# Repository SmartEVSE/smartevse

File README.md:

SmartEVSE v1
=========

This repository is now for the older v1 of the module only.
All developement for the current version v2 of the module is taking place here:
[SmartEVSE-2](https://github.com/SmartEVSE/SmartEVSE-2)

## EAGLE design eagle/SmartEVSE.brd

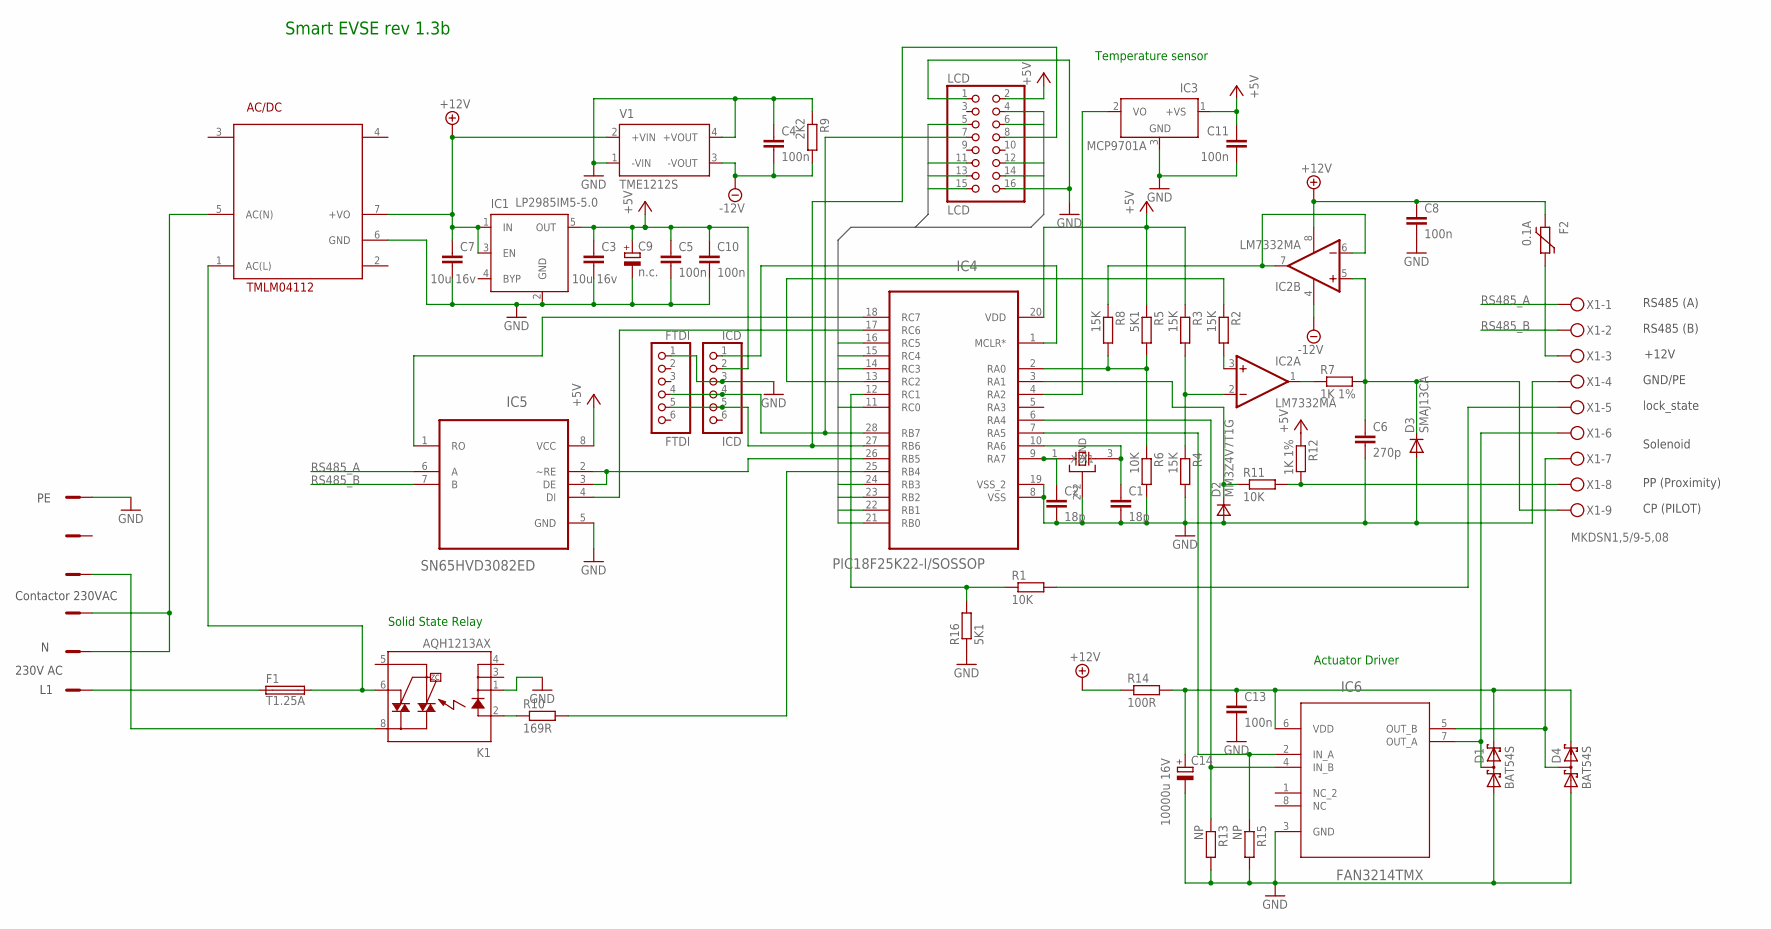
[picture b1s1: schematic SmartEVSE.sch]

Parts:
AC/DC: TMLM04112; AC/DC
C1, C2: 18p; C0805
C3, C7: 10u 16v; C1206
C4, C5, C8, C10, C11, C13: 100n; C0805
C6: 270p; C0805
C9: n.c.; SMC_C
C14: 10000u 16V; EB22,5D
D1, D4: BAT54S; SOT23
D2: MM3Z4V7T1G; SOD323
D3: SMAJ13CA; DO214AC
F1: T1.25A; TR5
F2: 0.1A; 1206L
FTDI: FTDI; 1X06
IC1: LP2985IM5-5.0; SOT23-5
IC2: LM7332MA; SO08
IC3: MCP9701A; SOT23
IC4: PIC18F25K22-I/SOSSOP; SOP65P780X200-28N
IC5: SN65HVD3082ED; SOIC127P600X175-8N
IC6: FAN3214TMX; SOIC127P600X175-8N
ICD: ICD; 1X06
K1: AQH1213AX; DIL07SMD
LCD: LCD; 2X08
Q1: CTS_32X25_SMD; CTS_32X25
R1, R6, R11: 10K; R0805
R2, R3, R4, R8: 15K; R0805
R5, R16: 5K1; R0805
R7, R12: 1K 1%; R0805
R9: 2K2; R0805
R10: 169R; R0805
R13, R15: NP; R0805
R14: 100R; R0805
V1: TME1212S; TME
X1: MKDSN1,5/9-5,08
X2: AST027-06; P_AST027-06

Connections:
+12V: AC/DC.7 (+VO), C7.1, C8.1, F2.P$1 (1), IC1.1 (IN), IC1.3 (EN), IC2.8 (V+), R14.1, V1.2 (+VIN)
-12V: C4.2, IC2.4 (V-), R9.2, V1.3 (-VOUT)
GND: AC/DC.6 (GND), C1.2, C2.2, C3.2, C4.1, C5.2, C6.2, C7.2, C8.2, C9.-, C10.2, C11.2, C13.2, C14.-, D1.1 (A1), D2.2 (A), D3.A, D4.1 (A1), FTDI.1, IC1.2 (GND), IC3.3 (GND), IC4.8 (VSS), IC4.19 (VSS_2), IC5.5 (GND), IC6.3 (GND), ICD.3, K1.1 (K), LCD.1, LCD.16, Q1.2 (GND), Q1.4 (GND), R4.2, R6.2, R9.1, R13.2, R15.2, R16.1, V1.1 (-VIN), V1.4 (+VOUT), X1.4, X2.P$1
LCD0: IC4.21 (RB0), LCD.11
LCD1: IC4.22 (RB1), LCD.12
LCD2: IC4.23 (RB2), LCD.13
LCD3: IC4.24 (RB3), LCD.14
LCD4: IC4.11 (RC0), LCD.15
LCD6: IC4.14 (RC3), LCD.4
LCD7: IC4.15 (RC4), LCD.5
LCD8: IC4.16 (RC5), LCD.6
unnamed: IC4.12 (RC1), R1.1, R16.2
unnamed: IC4.6 (RA4), IC6.4 (IN_B), R13.1
unnamed: IC4.17 (RC6), IC5.4 (DI)
unnamed: IC4.18 (RC7), IC5.1 (RO)
unnamed: C2.1, IC4.9 (RA7), Q1.1 (X1)
unnamed: C1.1, IC4.10 (RA6), Q1.3 (X2)
unnamed: IC2.2 (-IN), R3.2, R4.1
unnamed: C6.1, D3.C, IC2.5 (+IN), R7.2, X1.9
unnamed: IC4.13 (RC2), R2.1
unnamed: IC2.3 (+IN), R2.2
unnamed: IC4.2 (RA0), R5.2, R6.1, R8.2
unnamed: IC2.1 (OUT), R7.1
unnamed: IC2.6 (-IN), IC2.7 (OUT), R8.1
unnamed: D2.1 (C), IC4.3 (RA1), R11.1
unnamed: C13.1, C14.+, D1.2 (C2), D4.2 (C2), IC6.6 (VDD), R14.2
unnamed: IC4.7 (RA5), IC6.2 (IN_A), R15.1
unnamed: K1.2 (A), R10.1
unnamed: IC4.25 (RB4), R10.2
unnamed: AC/DC.1 (AC(L)), F1.2, K1.6 (DS3)
unnamed: R11.2, R12.2, X1.8
unnamed: K1.8 (DS1), X2.P$3
unnamed: F1.1, X2.P$6
unnamed: IC4.26 (RB5), IC5.2 (~RE), IC5.3 (DE)
unnamed: AC/DC.5 (AC(N)), X2.P$4, X2.P$5
unnamed: D1.3 (C1A2), IC6.7 (OUT_A), X1.6
unnamed: IC4.1 (MCLR*), ICD.1
unnamed: D4.3 (C1A2), IC6.5 (OUT_B), X1.7
unnamed: IC3.2 (VO), IC4.4 (RA2)
unnamed: F2.P$2 (2), X1.3
unnamed: R1.2, X1.5
unnamed: FTDI.4, IC4.28 (RB7), ICD.4, LCD.7
unnamed: FTDI.5, IC4.27 (RB6), ICD.5, LCD.8
RS485_A: IC5.6 (A), X1.1
RS485_B: IC5.7 (B), X1.2
VCC: C3.1, C5.1, C9.+, C10.1, C11.1, IC1.5 (OUT), IC3.1 (+VS), IC4.20 (VDD), IC5.8 (VCC), ICD.2, LCD.2, R3.1, R5.1, R12.1

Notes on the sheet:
230V AC
Solenoid
lock_state
+12V
CP (PILOT)
PP (Proximity)
GND/PE
RS485 (A)
RS485 (B)
Contactor 230VAC
Smart EVSE rev 1.3b
Temperature sensor
Actuator Driver
Solid State Relay

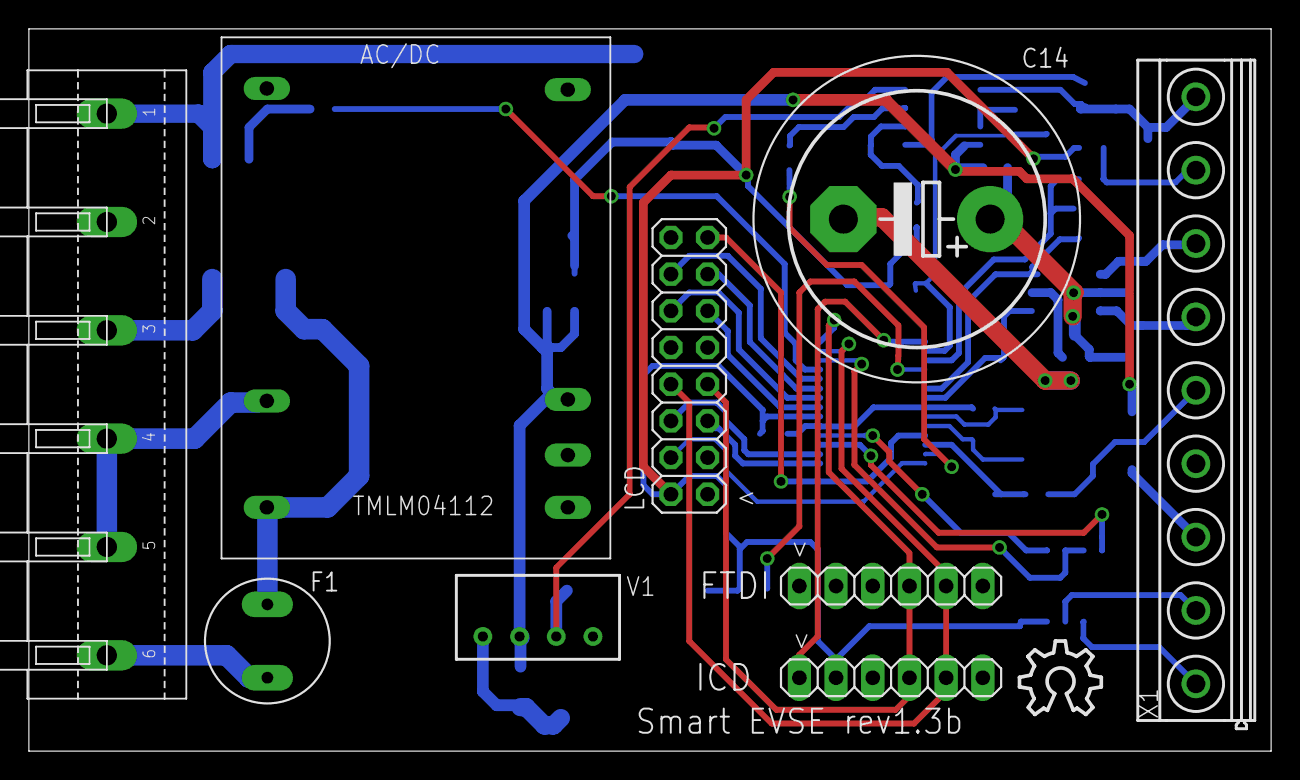
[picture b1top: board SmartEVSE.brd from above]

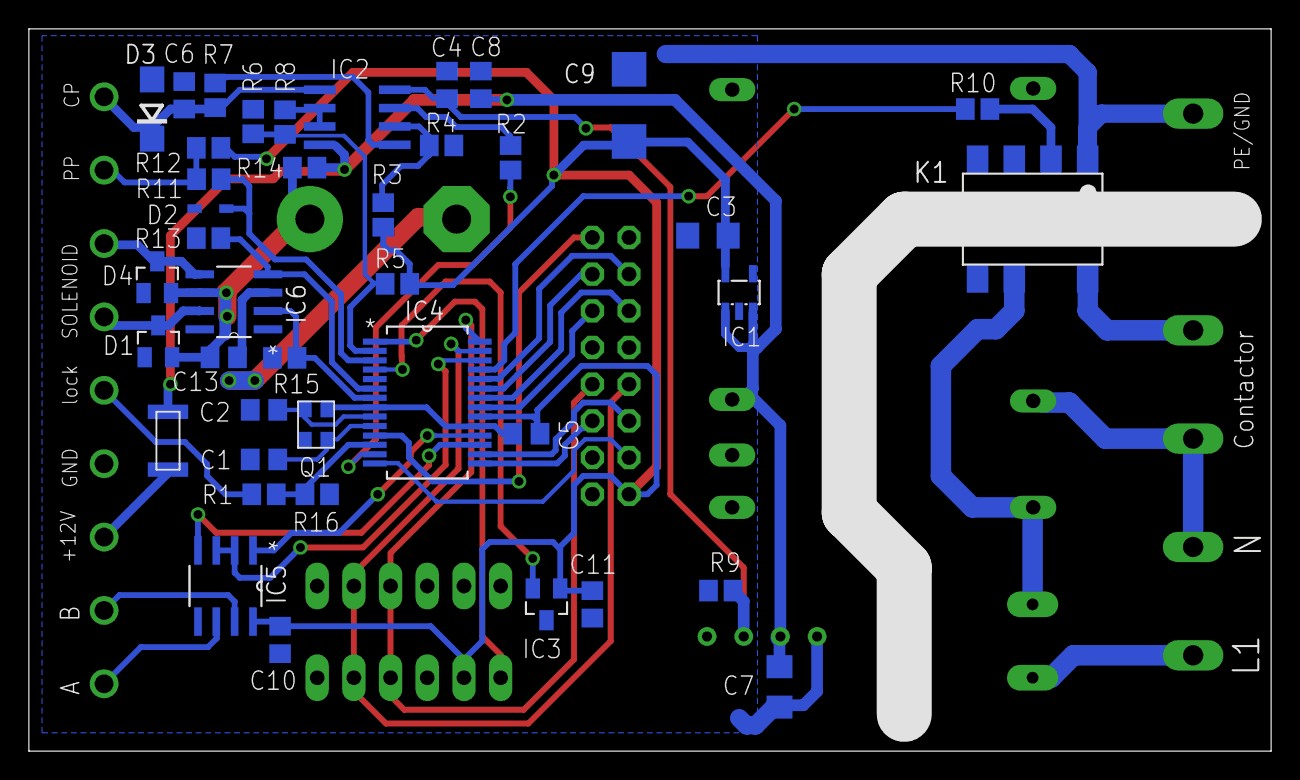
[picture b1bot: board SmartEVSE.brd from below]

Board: 2 copper layers, 86.0 x 50.0 mm, 51 parts (41 on the bottom side), 46 nets.

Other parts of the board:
U$1: OSHW_10X200_NOTEXT

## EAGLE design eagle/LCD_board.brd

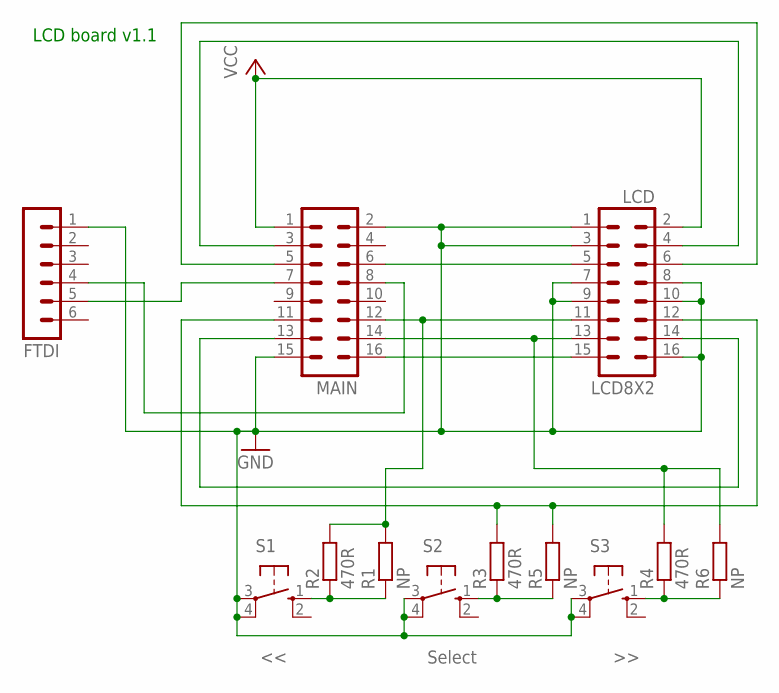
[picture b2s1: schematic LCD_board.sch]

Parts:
FTDI: MA06-1
LCD8X2: LCD; MA08-2
MAIN: MA08-2
R1, R5, R6: NP; 0204/7
R2, R3, R4: 470R; R0805
S1: <<; B3F-10XX
S2: Select; B3F-10XX
S3: >>; B3F-10XX

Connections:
GND: FTDI.1, LCD8X2.1, LCD8X2.3, LCD8X2.7, LCD8X2.8, LCD8X2.9, LCD8X2.10, LCD8X2.16, MAIN.2, MAIN.15, S1.3, S1.4 (P1), S2.3, S2.4 (P1), S3.3, S3.4 (P1)
unnamed: FTDI.5, MAIN.7
unnamed: LCD8X2.15, MAIN.16
unnamed: LCD8X2.13, MAIN.14, R4.2, R6.2
unnamed: LCD8X2.11, MAIN.12, R1.2, R2.2
unnamed: LCD8X2.14, MAIN.13
unnamed: LCD8X2.12, MAIN.11, R3.2, R5.2
unnamed: LCD8X2.5, MAIN.6
unnamed: LCD8X2.6, MAIN.5
unnamed: LCD8X2.4, MAIN.3
unnamed: FTDI.4, MAIN.8
unnamed: R1.1, R2.1, S1.1 (S)
unnamed: R3.1, R5.1, S2.1 (S)
unnamed: R4.1, R6.1, S3.1 (S)
VCC: LCD8X2.2, MAIN.1

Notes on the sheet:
LCD board v1.1

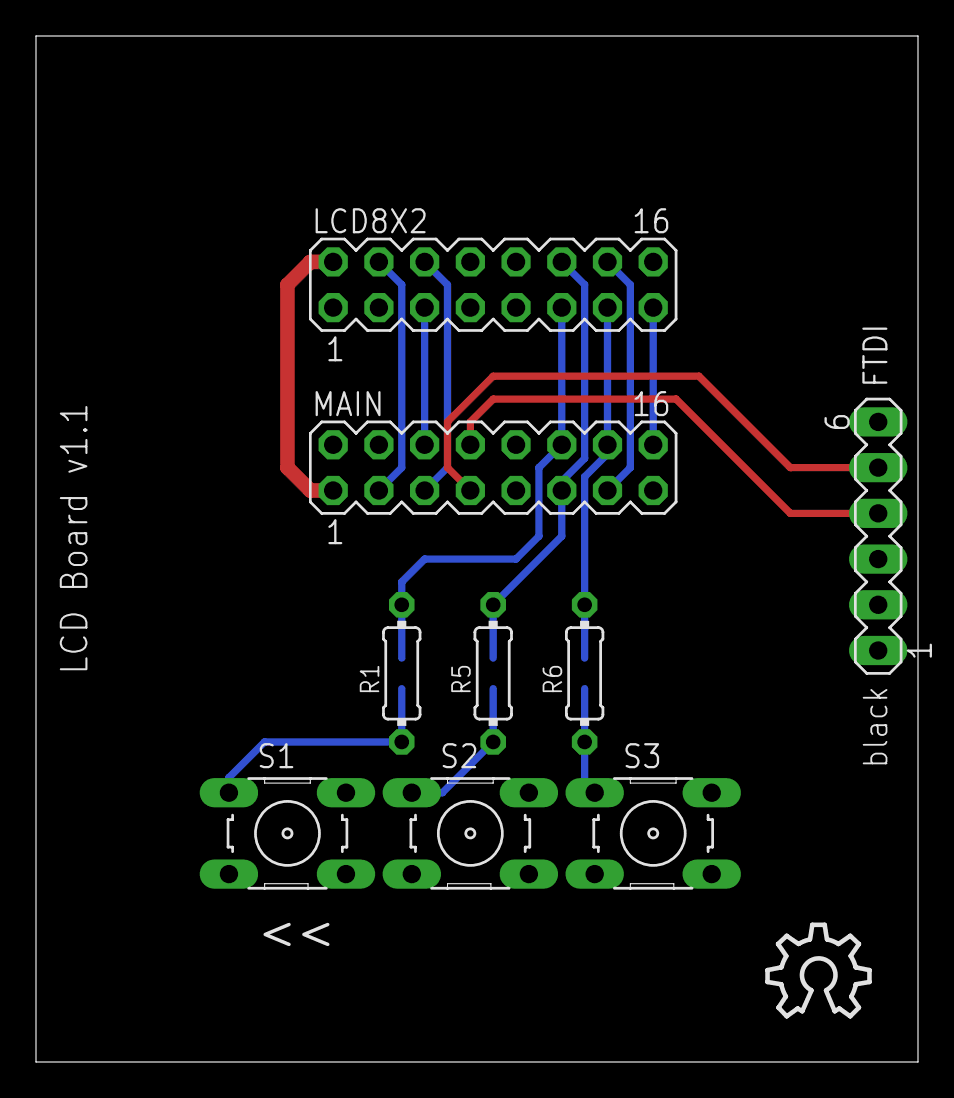
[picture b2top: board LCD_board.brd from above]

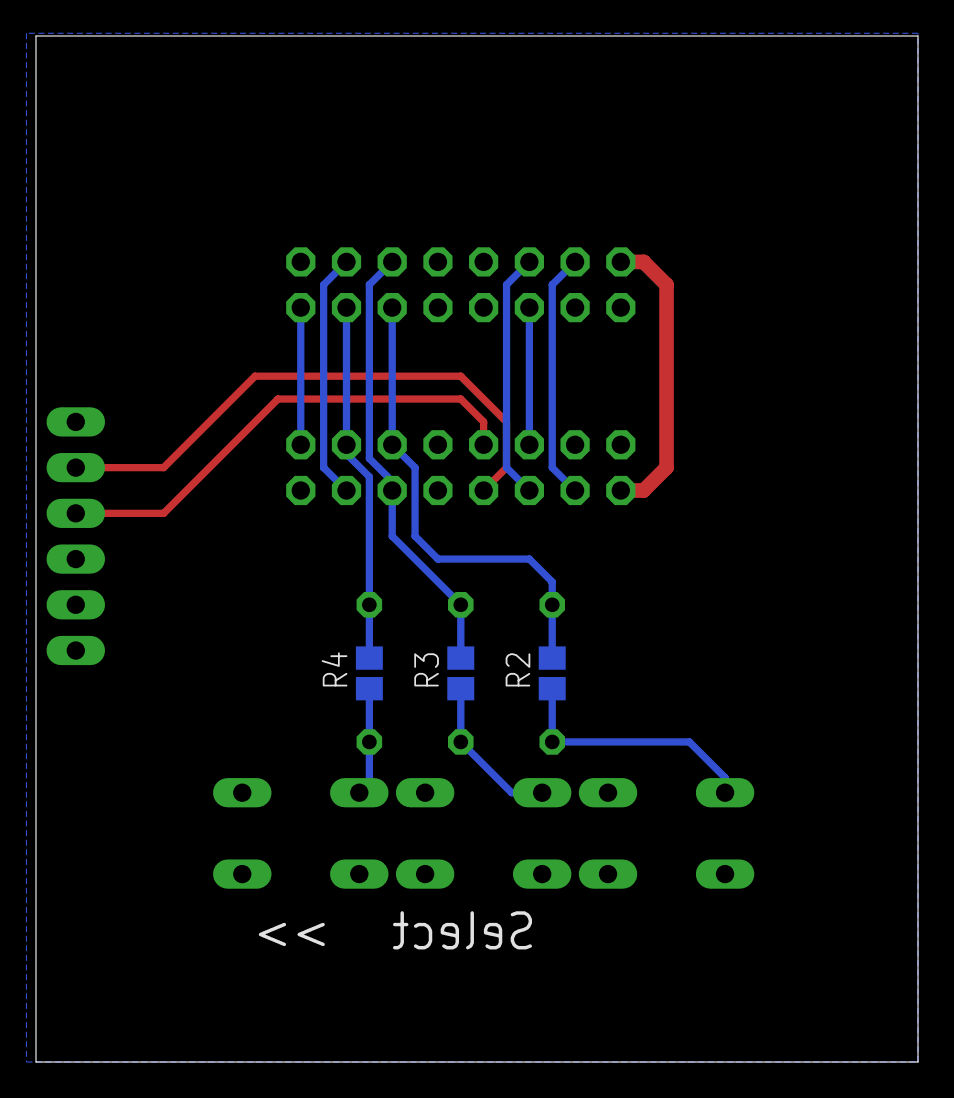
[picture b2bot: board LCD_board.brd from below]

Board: 2 copper layers, 49.0 x 57.0 mm, 13 parts (3 on the bottom side), 15 nets.

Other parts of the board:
U$1: OSHW_10X200_NOTEXT

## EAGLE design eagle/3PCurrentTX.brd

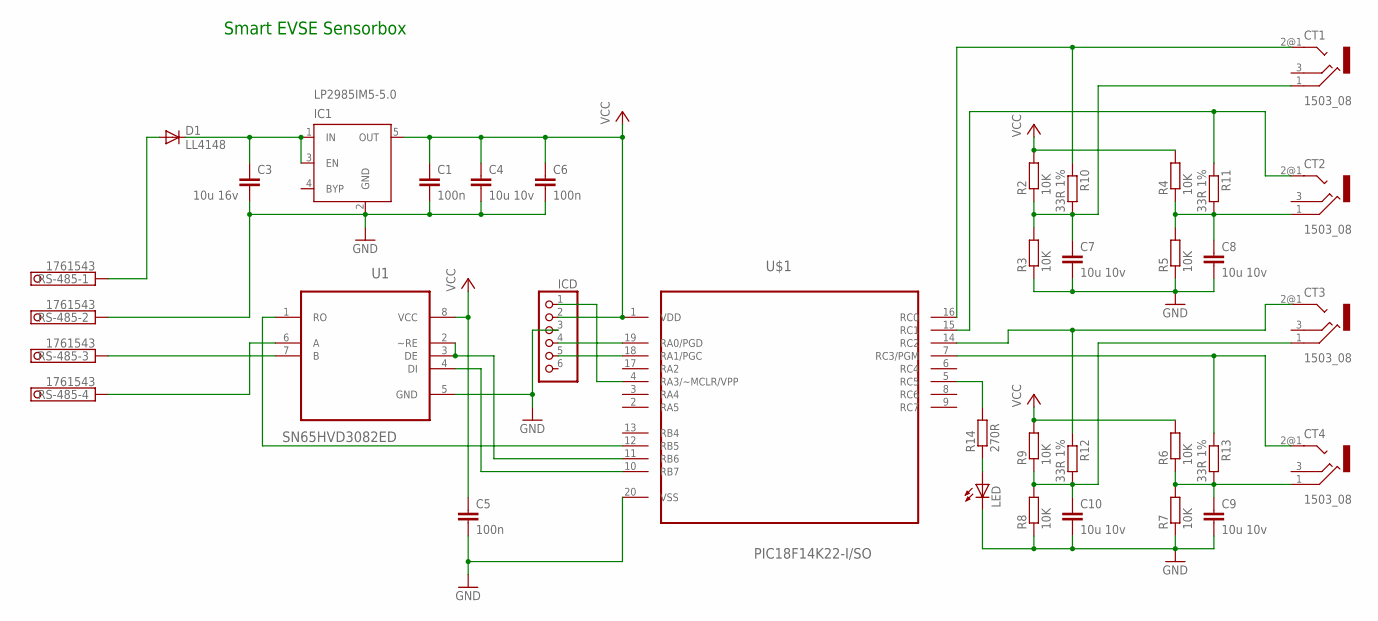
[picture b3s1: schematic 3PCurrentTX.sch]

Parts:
C1, C5, C6: 100n; C0805K
C3: 10u 16v; C1206K
C4, C7, C8, C9, C10: 10u 10v; C0805K
CT1, CT2, CT3, CT4: 1503_08
D1: LL4148; SOD123
IC1: LP2985IM5-5.0; SOT23-5
ICD: PINHD-1X6; 1X06
LED: LEDSML0805; SML0805
R2, R3, R4, R5, R6, R7, R8, R9: 10K; R0805
R10, R11, R12, R13: 33R 1%; R0805
R14: 270R; R0805
RS-485: 1761543; 1751264
U1: SN65HVD3082ED; SOIC127P600X175-8N
U$1: PIC18F14K22-I/SO; SOIC127P1030X265-20N; MPN PIC18F14k22-I/SO

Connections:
GND: C1.2, C3.2, C4.2, C5.2, C6.2, C7.2, C8.2, C9.2, C10.2, IC1.2 (GND), ICD.3, LED.C, R3.1, R5.1, R7.1, R8.1, RS-485.2, U1.5 (GND), U$1.20 (VSS)
unnamed: D1.A, RS-485.1
unnamed: R14.2, U$1.5 (RC5)
unnamed: U1.1 (RO), U$1.12 (RB5)
unnamed: U1.4 (DI), U$1.10 (RB7)
unnamed: U1.2 (~RE), U1.3 (DE), U$1.11 (RB6)
unnamed: CT1.2@1 (2), R10.1, U$1.16 (RC0)
unnamed: LED.A, R14.1
unnamed: CT3.2@1 (2), R12.1, U$1.14 (RC2)
unnamed: CT4.2@1 (2), R13.1, U$1.7 (RC3/PGM)
unnamed: CT2.2@1 (2), R11.1, U$1.15 (RC1)
unnamed: RS-485.3, U1.7 (B)
unnamed: RS-485.4, U1.6 (A)
unnamed: C7.1, CT1.1, R2.1, R3.2, R10.2
unnamed: C3.1, D1.C, IC1.1 (IN), IC1.3 (EN)
unnamed: ICD.5, U$1.18 (RA1/PGC)
unnamed: C8.1, CT2.1, R4.1, R5.2, R11.2
unnamed: ICD.1, U$1.4 (RA3/~MCLR/VPP)
unnamed: C10.1, CT3.1, R8.2, R9.1, R12.2
unnamed: C9.1, CT4.1, R6.1, R7.2, R13.2
unnamed: ICD.4, U$1.19 (RA0/PGD)
VCC: C1.1, C4.1, C5.1, C6.1, IC1.5 (OUT), ICD.2, R2.2, R4.2, R6.2, R9.2, U1.8 (VCC), U$1.1 (VDD)

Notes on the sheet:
Smart EVSE Sensorbox

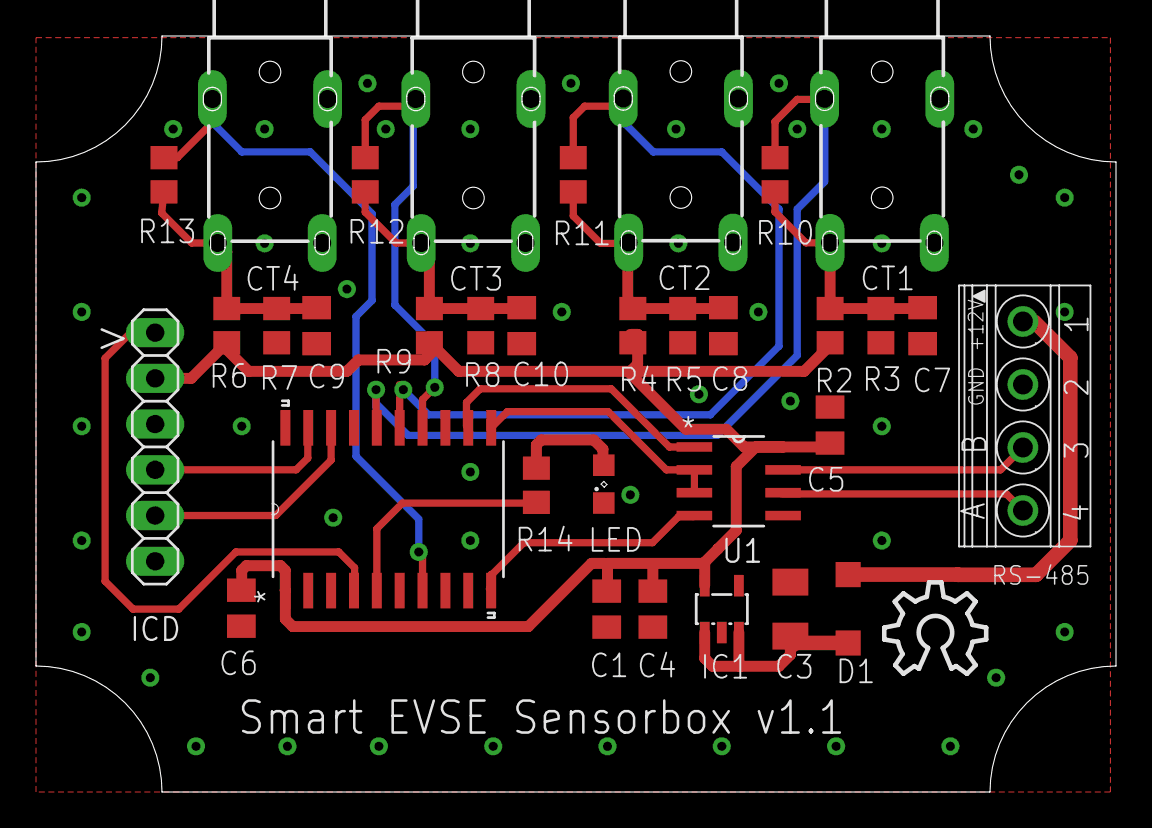
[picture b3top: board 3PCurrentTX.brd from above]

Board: 2 copper layers, 60.0 x 42.0 mm, 34 parts (0 on the bottom side), 22 nets.

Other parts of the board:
U$2: OSHW_10X200_NOTEXT

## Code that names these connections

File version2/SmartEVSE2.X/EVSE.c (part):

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        delay(3000);                                                            // wait 3 seconds for capacitor to charge

        CCP1CON = 0;                                                            // PWM off
        PORTCbits.RC2 = 0;                                                      // Control pilot static -12V
        delay(100);                                                             // wait 100 msec
        if (ReadPilot() == PILOT_DIODE) TestState = STATE_B;                    // should be -12V
        else error = 1;
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        TRISB = 0b10000101;                                                     // RB7(RX2), RB0,2 inputs. all other output
        LATBbits.LATB1 = 1;                                                     // set IO3 to high
        delay(5000);                                                            // wait 5 seconds for capacitor to charge
        if (PORTCbits.RC1 == 1) error ^= 4;                                     // error, Solenoid not activated !

        delay(10);
                                                                                // Contactor + I/O test
        if (PORTBbits.RB2 == 1)                                                 // sample input PIN IO2
        {
            LATBbits.LATB1 = 0;
            delay(10);
            if (PORTBbits.RB2 != 0) error ^= 8;                                 // error
        } else error ^= 8;                                                      // error

        TestState = STATE_CB;
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    } else if (TestState == STATE_CB && State == STATE_B) {
        TRISB = 0b10000001;                                                     // RB7(RX2), RB0 inputs. all other output
        delay(1000);
        if (PORTCbits.RC1 == 0) error ^= 4;                                     // Solenoid FAIL!!
        else if (!error) {
            TestState = 80;
            Lock = 0;
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    PMD2 = 0b00000000;

    PORTA = 0;                                                                  // Init PORTA
    ANSELA = 0b00000111;                                                        // RA0, RA1, RA2 are analog inputs (pin 2,3,4)
    TRISA = 0b00000111;                                                         // Set RA0,RA1,RA2 as inputs

    PORTB = 0;
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        
        BlinkLed();                                                             // Handle the blinking of the 12V LED

        TRISC = 0b10100011;                                                     // Set RC5 and RC0 to input. Make sure there are pull-ups on these pins.
        NOP();
        NOP();
        x = (PORTC & 0b00100001);                                               // Read Two Button Inputs on RC5(>) and RC0(select)
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
        if (RCmon == 1 && PORTBbits.RB1 == 1)                                   // RCD monitor active, and RCD DC current > 6mA ?
        {
           if (PORTBbits.RB1 == 1) {                                            // check again, to prevent voltage spikes from tripping the RCD detection (2.07)
                State = STATE_A;
                Error = RCD_TRIPPED;
                LCDTimer = 0;                                                   // display the correct error message on the LCD
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        if (State == STATE_A)                                                   
        {
            CCP1CON = 0;                                                        // PWM off
            PORTCbits.RC2 = 1;                                                  // Control pilot static +12V
            CONTACTOR_OFF;                                                      // Contactor OFF
            BalancedState[0] = 0;                                               // Mark as inactive

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                    State = STATE_ACTSTART;
                    ActivationTimer = 3;
                    CCP1CON = 0;                                                // PWM off
                    PORTCbits.RC2 = 0;                                          // Control pilot static -12V
                    INFO_PRINT("Activation Mode Triggered\r\n");
                }
                NextState = 0;                                                  // no State to switch to
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        
        if (State == STATE_ACTSTART && ActivationTimer == 0) {
            State = STATE_B;                                                    // Switch back to State B
            PORTCbits.RC2 = 1;                                                  // Control pilot static +12V
            ActivationMode = 255;                                               // Disable ActivationMode
            STATE_PRINT("STATE ACTSTART");
        }
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
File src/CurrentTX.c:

/*
;    Project:       3+ Phase Current Transmitter, for use with Smart EVSE
;    Date:          16 October 2013
;
;    Changes:
;    1.0  Initial release
;
;    (C) 2013  Michael Stegen / Stegen Electronics
;
;	 RMS current measurement calculation, from openenergymonitor.org
;
;
; Permission is hereby granted, free of charge, to any person obtaining a copy
; of this software and associated documentation files (the "Software"), to deal
; in the Software without restriction, including without limitation the rights
; to use, copy, modify, merge, publish, distribute, sublicense, and/or sell
; copies of the Software, and to permit persons to whom the Software is
; furnished to do so, subject to the following conditions:
;
; The above copyright notice and this permission notice shall be included in
; all copies or substantial portions of the Software.
;
; THE SOFTWARE IS PROVIDED "AS IS", WITHOUT WARRANTY OF ANY KIND, EXPRESS OR
; IMPLIED, INCLUDING BUT NOT LIMITED TO THE WARRANTIES OF MERCHANTABILITY,
; FITNESS FOR A PARTICULAR PURPOSE AND NONINFRINGEMENT. IN NO EVENT SHALL THE
; AUTHORS OR COPYRIGHT HOLDERS BE LIABLE FOR ANY CLAIM, DAMAGES OR OTHER
; LIABILITY, WHETHER IN AN ACTION OF CONTRACT, TORT OR OTHERWISE, ARISING FROM,
; OUT OF OR IN CONNECTION WITH THE SOFTWARE OR THE USE OR OTHER DEALINGS IN
; THE SOFTWARE.
*/


#include "p18f14k22.h"
#include <stdio.h>
#include <math.h>


// Configuration settings
#pragma	config FCMEN = OFF,	IESO = OFF, PCLKEN = ON
#pragma config PLLEN = ON, FOSC = IRC
#pragma	config BORV = 30, BOREN = OFF, PWRTEN = ON
#pragma	config WDTPS = 2048, WDTEN = OFF     // WDT timeout
#pragma config MCLRE  = OFF, HFOFST = OFF
#pragma config XINST = ON, BBSIZ = OFF, LVP = OFF, STVREN = ON
#pragma	config CP0 = OFF, CP1 = OFF, CPD = OFF, CPB = OFF
#pragma	config WRT0 = OFF, WRT1 = OFF
#pragma	config WRTD = OFF, WRTB = OFF, WRTC = OFF
#pragma	config EBTR1 = OFF, EBTR0 = OFF
#pragma	config EBTRB = OFF

// Global data
#pragma udata

#define VERSION 1
#define SAMPLES 2048				// Samples per channel
#define BAUD1K2						// Baudrate 1200 bps
#define NR_CTS	3					// Number of CT's	

char buffer[50];
double Irms[NR_CTS];
unsigned int lastSampleI,sampleI;   //sample_ holds the raw analog read value, lastSample_ holds the last sample
double lastFilteredI, filteredI;	//Filtered_ is the raw analog value minus the DC offset

unsigned int sampleI_CT[NR_CTS]={512,512,512};
double filteredI_CT[NR_CTS]={0,0,0};



void UartTX(char byte) 
{
	// output one byte 
	while(!PIR1bits.TXIF)			// set when register is empty 
		continue;
	TXREG = byte;
}

/*
void UartTXHex(unsigned char c)
{
	unsigned char h;
	
	h = (c>>4);
	if (h>9) h+=7;
	h+='0';						// conversion to ASCII
	UartTX(h);					// TX 

	h = c & 0x0f;
	if (h>9) h+=7;
	h+='0';						// conversion to ASCII
	UartTX(h);
}
*/



// calculates 16-bit CRC of given data
// used for Frame Check Sequence on data frame
// Poly used is x^16+x^12+x^5+x
unsigned int calc_crc16(char* start, char len)
{
	unsigned int crc=0xffff,c;
	int i;
	while(len--)
	{
  		c=*start;
  		for(i=0;i<8;i++)
		{
   			if((crc ^ c) & 1) crc=(crc>>1)^0x8408;
   			else crc>>=1;
   			c>>=1;
  		}
  		start++;
 	}
	crc = (unsigned int)(crc ^ 0xFFFF);
 	return(crc);
}




void UART_RX(void)
{
	char x;
	x = RCREG;						// read USART byte to clear PIR1bits.RCIF flag
									// No further processing is done at this time 
}


/*  Send buffer over RS485. Use PPP in HDLC-like Framing for transfers
;   for protocol spec see: http://tools.ietf.org/html/rfc1662
;   compatible with existing RS485 line used on SMA solar inverters.
;
; 	baudrate is 1200 bps
; 	
;	<protocol>,<version>,<nr of samples>,<sample 1>...<sample n>,<crc16>
;   protocol = 0x5001 (2 bytes)
;	version = 0x01 (1 byte) 
;	nr of channels = 1 byte
;	samples are 4 bytes (double)
;	crc16 is 2 bytes
;
;	total 4+(n*4)+2 bytes (+ HDLC overhead)
;
*/
void UART_SendBuf(char* buffer, unsigned char len)
{
	char ch;
	PORTBbits.RB6 = 1;					// set RS485 transceiver to transmit
	UartTX(0x7E);						// transmit sync flag

	while(len--)			
	{
		ch = *buffer++;					// load next byte
		if ((ch == 0x11) || (ch == 0x12) || (ch == 0x13) || (ch == 0x7E) || (ch == 0x7D))	// check for escape character
		{
			ch = ch^0x20;
			UartTX(0x7D);				// transmit escape character
		}
		UartTX(ch);						// transmit byte
	}
	
	UartTX(0x7E);						// transmit sync flag

	while (!TXSTAbits.TRMT)	continue;	// transmit register empty?
	PORTBbits.RB6 = 0;					// set RS485 transceiver to receive

}



unsigned int ReadAnalog(void)	// Start ADC conversion, and return result
{
	ADCON0bits.GO=1;						// initiate conversion on the selected channel
	while(ADCON0bits.GO);
	return ADRES;							// return result
}

double ReadCT(unsigned char Ch)
{
	unsigned int n;
	double sumI;			//sum = Sum
	unsigned char ADCch;

	ADCch=Ch+4;				// Set ADC channel
	ADCch=(ADCch<<2)+1;		// shift 2 pos to left, enable ADC
	ADCON0=ADCch;			// channel select

	sumI = 0;

	sampleI=sampleI_CT[Ch];										// Get Sample and Filter values
	filteredI=filteredI_CT[Ch];	

	for (n = 0; n < SAMPLES; n++)
  	{
    	lastSampleI = sampleI;									// Used for offset removal
    	sampleI = ReadAnalog();									// Read port RAx 
    	lastFilteredI = filteredI;								// Used for offset removal
    	filteredI = (0.996*(lastFilteredI+sampleI-lastSampleI)); 	// Digital high pass filters to remove 2.5V DC offset. 
		
		// Root-mean-square method current
	   	// 1) square current values
       	// 2) sum 
    	sumI += (filteredI * filteredI);
	}

	sampleI_CT[Ch]=sampleI;
	filteredI_CT[Ch]=filteredI;									// Store Sample and Filter values

	return (sqrt(sumI / SAMPLES));								// Return squareroot of uncalibrated value

}

void init(void)
{
	OSCCON = 0b11100000;	// setup 32Mhz internal oscillator (max 64Mhz)
	PORTA = 0; 				// Init PORTA
 	LATA = 0;
	ANSEL = 0b11110000;		// RC0, RC1, RC2, RC3 are analog inputs (pin 16,15,14,7)
	ANSELH = 0;				// All digital IO
	TRISA = 0b00100000;		// Set UART RX as input
	PORTC = 0;
	TRISC = 0b00001111;		// RC0-RC3 analog inputs
	PORTB = 0;
	TRISB = 0b00000000;		// all outputs



#if defined(BAUD19K2)
	SPBRGH = 1;				// Initialize UART
	SPBRG = 160;			// Baudrate 19k2 
#endif
#if defined(BAUD4K8)
	SPBRGH = 6;				// Initialize UART
	SPBRG = 130;			// Baudrate 4800
#endif	
#if defined(BAUD1K2)
	SPBRGH = 0x1A;			// Initialize UART
	SPBRG = 0x0A;			// Baudrate 1200
#endif	
	BAUDCON = 0b00001000;	// 16 bit Baudrate register is used
	TXSTA = 0b00100100;		// Enable TX, 8 bit, Asynchronous mode
	RCSTA = 0b10010000;		// Enable serial port TX and RX, 8 bit. 

	ADCON0 = 0;				// ADC disabled for now
	ADCON1 = 0;
	ADCON2 = 0b10000010;	// Right justify, Tacq = 0 uS, FOSC/32

	T0CON = 0b10000111;		// @ 8Mhz => 32 uS Timer0, 16 bit counter

}

void main(void)
{
	char *pBytes;
	char x,n;
	unsigned int cs;

	init();						// initialize ports, ADC, UART
	
	for (x=0;x<NR_CTS;x++)				// initialize the CT's / ADC registers
			Irms[x] = ReadCT(x);		// Read CT1..CTX, and ignore..


	while(1)
	{
		for (x=0;x<NR_CTS;x++)
			Irms[x] = ReadCT(x);		// Read CT1..CTX

		TMR0H =0;
		TMR0L =0;						// reset timer 0

		do {
			if (PIR1bits.RCIF)			// Uart Reception?
			{
				UART_RX();				// yes, read received byte
				TMR0H =0;
				TMR0L =0;				// reset timer 0
			}
			if (RCSTAbits.OERR)			// Uart Overrun Error?
			{
				RCSTAbits.CREN = 0;
				RCSTAbits.CREN = 1;		// Restart Uart
			}
			x= TMR0L;					// Read TMR0 
		} while (TMR0H < 5);			// no data on RS485 line for 40 ms 

										// Setup HDLC frame
		buffer[0]= 0xff;				// Address Field = ff
		buffer[1]= 0x03;				// Control Field = 03
		buffer[2]= 0x50;				// Protocol = 0x5001
		buffer[3]= 0x01;
		buffer[4]= VERSION;
		buffer[5]= NR_CTS;

		n=6;
		for (x=0;x<NR_CTS;x++)
		{	
			pBytes = (char*)&Irms[x];	// get raw 4 byte Double 
			buffer[n++] = (pBytes[0]);
			buffer[n++] = (pBytes[1]);
			buffer[n++] = (pBytes[2]);
			buffer[n++] = (pBytes[3]);
		}
										// Frame Check Sequence (FCS) Field
		cs = calc_crc16(buffer, n);		// calculate CRC16 from data			
		buffer[n++] = ((unsigned char)(cs));
		buffer[n++] = ((unsigned char)(cs>>8));	

		PORTCbits.RC5=1;				// LED on
		UART_SendBuf(buffer,n);			// send buffer to RS485 port
		PORTCbits.RC5=0;				// LED off

	//	printf("CT1:%5d CT2:%5d CT3:%5d\r\n",(int)(Irms[0]*100), (int)(Irms[1]*100), (int)(Irms[2]*100));
	}
 

}

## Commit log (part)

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2014-01-07 First commit of Smart EVSE
2014-01-20 Second commit of Smart EVSE
2015-07-04 doc: Add CLI docs
2015-07-04 doc: Add a picture with a TTL cable connected
2016-02-23 Version 1.04
    Changed menu so that only relevant options are shown. Added option for fixed cable installations. (no Cable Lock, override PP pin) ;
2016-03-15 version 1.06, Improved Smartmode current regulation
2016-06-10 version 1.07 Added Load balancing option for 2-4 SmartEVSE's.
2017-08-28 Smart EVSE v2 code and pcb files
2018-04-26 Changed minimal MaxMains value to 16A
    See https://github.com/SmartEVSE/smartevse/issues/7
2018-10-08 Add picture SmartEVSEv2
2018-11-03 Whitespace changes
    I saw that the file was mixing tabs and spaces for indentation.
    As I was fixing that, I also went a bit overboard with the outlining of the comments :-)
2019-02-18 Version 2.04
    In version 2.04 we added support for external stop button, a 12V LED on IO1.
    The external 12V LED requires a hardware change (hw ver 2.1)
2019-02-24 typo
2019-04-24 V2.06
    Firmware version 2.06
2019-05-13 Change some lines to windows line ending
2019-05-13 Automate LCD menu generation for easier code reading and maintenance
2019-05-14 Add experimental modbus functions
2019-05-22 Bugfix: Cant navigate back from the lowest value to the highest if the lowest value is 0
2019-05-26 Add Solar mode and animated graphic
2019-05-26 Simplify GLCDMenu by creating a MenuItems array and navigate through the array
2019-05-27 - Create an global MenuStr struct with all menu strings - Simplify GLCDHelp by renumbering MENU_xxx and use the value as index in MenuStr - Use var MenuStr, MenuItems and const MENU_xxx in RS232cli
2019-05-28 Implement modbus protocol
2019-05-28 Some cleanups
2019-05-29 Bugfixes - Move U1packet buffer into main loop - Modbus packet length check - Modbus request response detection - Reset no communication timer on broadcast receive
2019-05-29 - Use a struct for modbus information - Extract modbus decoding to a function
2019-05-30 Bugfix: Send Modbus Requests only on Load Balancing: Disabled or Master
2019-06-01 Multiplier 10 on ChargeCurrent missing on some lines
2019-06-01 Switch modbus receive packets from SmartEVSE in 3 categories: DataReceived = 1 : Measurement from electric meter DataReceived = 2 : Communication from Master to Slave DataReceived = 3 : Communication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
2019-06-02 Modbus implementation to read and set configuration options: Register 0xC*: Configuration 0xC0: CONFIG 0xC1: MODE 0xC2: START 0xC3: STOP 0xC4: LOADBL 0xC5: MIN 0xC6: CABLE 0xC7: LOCK 0xC8: ACCESS 0xC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
2019-06-02 Use get/setMenuItemValue in LCD navigation to reduce code in GLCDMenu
2019-06-03 Remove unused function MenuNavChar
2019-06-03 Bugfix: Do not show help on EXIT MENU
2019-06-04 Create function "updateCurrentData" for processing received current measurement
2019-06-04 Bugfix: Show MAINS and MIN option also in load balancing mode
2019-06-07 Create struct EMConfig to store EM configurations. - Renumber EM IDs to simplify code - Remove EM option "Disabled" as it is mandatory
2019-06-07 Update README.MD with electric meter and modbus informations.
2019-06-07 Insert table for modbus registers in README.md
2019-06-07 Typo in README.md
2019-06-08 Extend pow10 to handle positive and negative values
2019-06-09 Add possibility to configure custom electric meter
2019-06-10 Update README.md with additional modbus registers for custom electric meter
2019-06-10 Correct values in modbus register check
2019-06-10 Bugfix: Use variable CT1 in GLCD sensorbox calibration instead of ICal
2019-06-10 Avoid variable conversion to reduce compiler warnings
2019-06-12 Define IsetBalance as signed int as it can get negative
2019-06-13 Wait for IO2 state change until trigger action
2019-06-14 Add Switch option "Smart-Solar" to choose with an external switch between smart and solar charging Rename Access variable/constant to Switch
2019-06-15 For switch mode Smart-Solar device must be in Solar mode
2019-06-15 Add support for electric meter Eastron SDM630
2019-06-15 Add Switch IO2 option for Access Switch and Smart-Solar Push-Button
2019-06-15 Also don't reset Access_bit if Switch is Access Switch
2019-06-15 Save litte memory by using an array for Load Balancing option strings
2019-06-16 Differ between Sensorbox 2 with P1 or CT data
2019-06-16 Bugfix in Modbux FC=16 write multiple
2019-06-16 Always show config option "MAX" as it can also limit current on Slave EVSE
2019-06-19 Eastron SDM630 current is unsigned -> Get sign from power register
2019-06-20 Remove double check of ISRTXFLAG in RS485SendBuf
2019-06-20 Remove Sensorbox v1 compatibility code
2019-06-20 Change EMConfig.IRegister type to unsigned int as EMConfig.ERegister
2019-06-20 Sensorbox calibration bugfixes
2019-06-20 Add visualisation for solar mode and solar stop timer
2019-06-20 Bugfix: Also write settings if set by broadcast
2019-06-21 Reordered modbus state variables to bundle load balancing relevant information
2019-06-25 Update EVSE mode on slave when changed by switch
2019-07-10 Show "Disable" instead of "0 min" on solar stop time
2019-07-23 Bugfixes
    Fixed Issues:
    - Check if sensorbox calibration procedures working
    - Slave should immediately disconnect power from cable on disconnect.
    Fixed Bugs:
    - clear chargedelay when switching from Solar to Smart Mode.
    - disable Solar stop timer when switching between Solar to Smart Mode.
2019-07-24 Check modbus register in response of electric meter
2019-10-31 V2.07 fixed RCD trip due to inductive loads.
    Bootloader can now only be entered when also the right button on top of the module is pressed.
    Added Compile time option to switch directly from STATE_A to STATE_C.
2019-11-08 Updated Schematics
    Updated schematic and board to version 2.2
2019-11-15 Updated manual to v1.11
    Updated Smart EVSE install manual to v1.11 for firmware version 2.10
2020-01-02 Version 2.12 fixes garbled LCD
    2.11 Fixed rare corrupted flash issue, seems to happen sometimes at power on.
    Bootloader also gets updated to fix this issue (now v1.06)
    MAX setting now starts at 6A
    2.12 Fixed garbled LCD.
2020-01-26 Master/Slave communication bug fixes.
    Various Master/Slave communication bug fixes.
    created utils/bootloader/math.c files, as the main sourcefile became too large
2020-01-28 version 2.14 Fixed Broadcast error message handling
    Fixed Broadcast error clear message handling on slave.
    Added check in Solar mode for overloading the MAINS.
    Removed START and STOP menu options from the slave, as it is determined by the master.
2020-06-04 version 2.16 Added Import / Grid menu option, bugfixes
    2.15 Added check to see if Sensorbox data contains new measurement data.
    - Added IMPORT menu option, which allows for power import from the grid when solar charging.
    - Added compile time option to compensate for 230V-400V transformers.
    - Added Activation mode, which is triggered if state C is not entered within 30 seconds.
    - If an external push button is used as Smart/Solar mode switch, holding this button for 1.5 seconds will now stop charging.
    2.16 Fixed Smart/Solar mode switch, it would force Solar or Smart mode, even in Normal mode.
2020-06-04 manual version 2.16
2020-06-08 version 2.17 Solar mode state switch bugfix. Hides the CAL menu when not used
    Fixed state switch bug while in solar mode.
    Hides CAL menu option when CT's are not used.
2020-09-02 allow to build with cmake using xc8 compiler no need for mplab
    mkdir build && cd build && cmake .. && make
2020-09-06 detect cable with Proximity Pilot defective
2020-09-06 show Errors on LCD
2020-09-06 add Internal Temperature to ModBUS (0xA9)
2020-09-06 improve menu infos
2020-09-09 add new Lock mode "Relay"
    Locked:
    W --> GND
    R --> 12V
    Unlocked:
    W --> GND
    R --> GND
2020-09-20 allow to disable MENU via Modbus Extended Configuration registeres (0xD0)
2020-09-20 make line endings consistent for printf output of modbus
2020-10-20 Show PV meter address option only if PV meter selected
2020-10-20 Use same variable in getMenuItemOption MENU_STOP case
2020-10-20 Remove ERegCount from EMConfig (Energy is stored most times in two bytes, more bytes not manageable)
2020-10-20 Initialize CalActive = 0 in receiveCurrentMeasurement
2020-10-22 Rename function GLCD_print2 to GLCD_print_buf2
2020-10-22 Comment font array
2020-10-23 - Remove leading zeros - Round measured values - Condense font
2020-10-23 - Add EV meter option - Display charged amount of energy
2020-10-25 Center message "READY" with chargedelay
2020-10-25 Cleanup function GLCD
2020-11-03 Removed erroneous ;
2020-11-03 Enabled reset via MCLR pin
2020-11-03 Add compile time option for modbus parity bits
2020-11-03 Modbus function 4=>3
2020-11-07 Added support for multiple parity settings and YTL meter
2020-11-07 Improvements for EV Meter - Fixed YTL byte order - Added phase currents to display - Error detection for all meters - Display Connected for STATE_B
2020-11-07 Reverted to INTMCLR
2020-11-10 Started implementing OpenEVSE RAPI
2020-11-11 Added sleep/enable/disable support Added sleep/disable state reporting
2020-11-15 Improved state reporting
2020-11-19 Added voltage measurement etc.
2020-11-20 Fixed last charge reporting
2020-11-20 Wait for PWM state to be certain not to miss it.
2020-11-25 Simplify functions pow10 and sprintfd
2020-11-30 Rewrite modbus communication between SmartEVSE
2020-12-01 Read serial number from flash
2020-12-01 Increased MaxMains to 200A, and Circuit to 160A
2020-12-01 Added setup menu navigation indicator
2020-12-02 Added RFID reader option
2020-12-02 Use constants for minimum and maximum modbus address of electric meter
2020-12-02 Declare variable at top of function crc16
2020-12-03 Extend EMConfig struct with Modbus function and voltage register information
2020-12-03 Use constants for size of MenuItems / MenuStr / EMConfig
2020-12-06 Update position of "kwh" and the menu arrow "<"
2020-12-06 Auto repeat button press when holding it down
2020-12-12 Define log levels
2020-12-12 Add ABB electric meter
2020-12-12 Move modbus functions to modbus.c
2020-12-13 Update README.md
    This would have saved me a lot of time ;)
2020-12-23 Change broadcast address, remove stateB in SlaveState handler
2020-12-23 Change files EVSE.* and GLCD.* to UNIX line endings
2020-12-24 Update modbus mapping
2020-12-24 Optimize calculation with separate PV electic meter
2020-12-24 Extend modbus debug information
2020-12-24 Move function GetPosInMenu to GLCD.c
2020-12-25 Enable EV electric meter for all SmartEVSE nodes
2020-12-25 Rename "Slave" to "Node"
2020-12-25 Replace printf line endings from Windows to UNIX
2020-12-27 Move new line character in LOG_* printf to the beginning
2021-01-14 Optimize EV electric meter poll
2021-01-14 Don't response on broadcast and save some program bytes
2021-01-14 Show real charging power in Smart/Solar mode
2021-01-15 Extend to 7 nodes
2021-01-15 Switch on backlight when removing charging cable
2021-01-16 Solve some compiler warnings
2021-01-16 Simplify GLCD text rotation and add charging power
2021-01-22 Use signed long instead of signed double for all measurements
2021-01-22 Save 58 program bytes
2021-01-22 Remove unused NOCURRENT error
2021-01-22 Bugfix: Extend Str in GLCD to 11 chars
2021-01-23 Use modbus status register for broadcast error and solar timer
2021-01-23 Create setSolarStopTimer function
2021-01-27 Some code cleanup
2021-01-28 Use signed int/long instead of signed double for all current calculations
2021-01-28 Filter only Sensorbox from EV electric meter
2021-01-28 Repeat button press after 0.5 second
2021-01-28 Cleanup file header include
2021-01-29 Save 12 bytes and some compiler warnings
2021-02-12 Moved SmartESVE-2 to it's own repository

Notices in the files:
version2/SmartEVSE2.X/EVSE.c:
(C) 2013-2020  Michael Stegen / Stegen Electronics
